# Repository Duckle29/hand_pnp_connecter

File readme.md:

# Hand Pick n Place glue board
This is just a small board I use to connect all the parts for my hand-vacuum pick and place tool. It connects a 12v vacuum pump, a 12v solenoid, a foot-switch, power-switch and power supply in a neat way.

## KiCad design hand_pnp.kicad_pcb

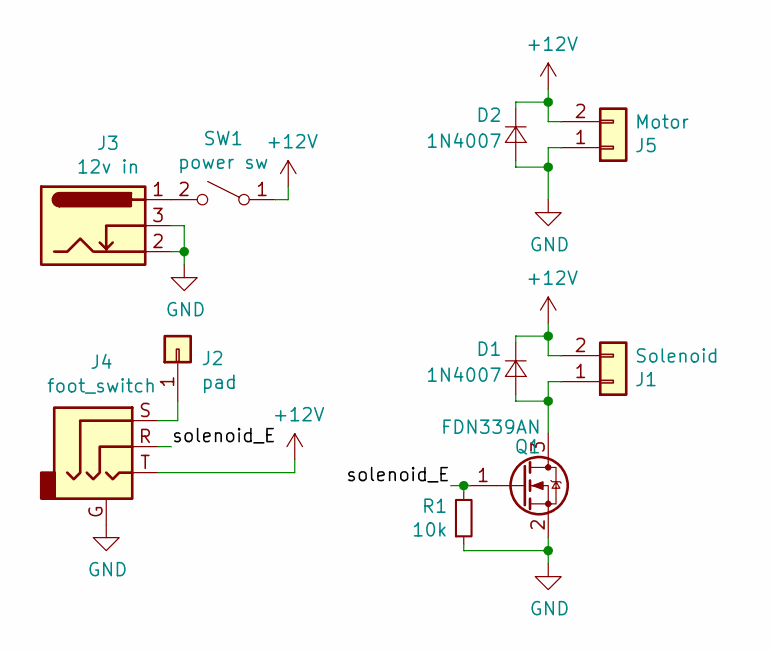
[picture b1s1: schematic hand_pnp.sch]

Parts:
D1, D2: 1N4007; D_DO-41_SOD81_P7.62mm_Horizontal
J1: Solenoid; PinHeader_1x02_P2.54mm_Horizontal
J2: pad; TestPoint_THTPad_1.5x1.5mm_Drill0.7mm
J3: 12v in; BarrelJack_Wuerth_6941xx301002
J4: foot_switch; Jack_3.5mm_CUI_SJ-3524-SMT_Horizontal
J5: Motor; PinHeader_1x02_P2.54mm_Vertical
Q1: FDN339AN; SOT-23
R1: 10k; R_0603_1608Metric_Pad1.05x0.95mm_HandSolder
SW1: power sw; PinHeader_1x02_P2.54mm_Horizontal

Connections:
+12V: D1.1 (K), D2.1 (K), J1.2, J4.T, J5.2, SW1.1 (A)
/solenoid_E: J4.R, Q1.1 (G), R1.2
GND: D2.2 (A), J3.2, J3.3, J4.G, J5.1, Q1.2 (S), R1.1
unnamed: D1.2 (A), J1.1, Q1.3 (D)
unnamed: J2.1, J4.S
unnamed: J3.1, SW1.2 (B)

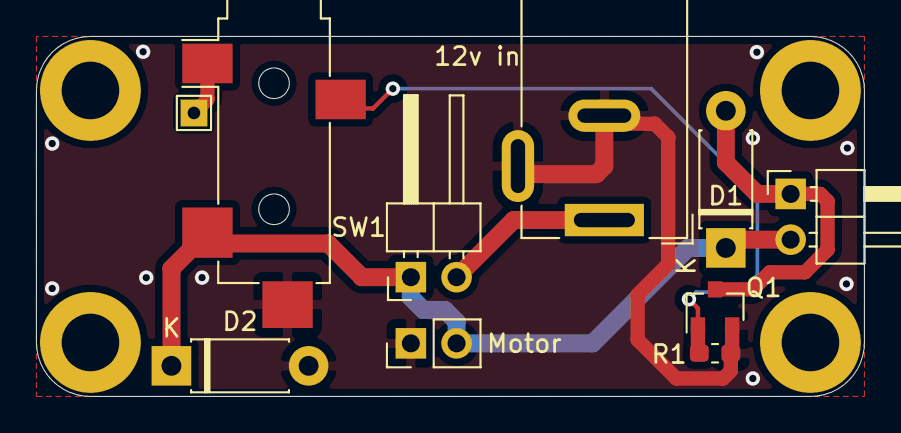
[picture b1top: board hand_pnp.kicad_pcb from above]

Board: 2 copper layers, 46.0 x 20.0 mm, 10 parts (0 on the bottom side), 6 nets.

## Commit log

2019-11-26 Initial commit of project
2019-11-26 Added renders, readme and gerbers
2019-11-26 Saved files
2019-11-28 Modified board to make it smaller
